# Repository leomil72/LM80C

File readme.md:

# LM80C Color Computer - A Z80-based homebrew computer

> This is the official repo of the **LM80C Color Computer**, an 8-bit home computer based on the Z80 CPU entirely developed since 2019 by **Leonardo Miliani**. Here you can find schematics, code and other stuff that you can use to replicate this project and build your own homebrew computer as a sort of "back to the old, good, days of 8-bit systems".
>
> Project main page: [LM80C](https://www.leonardomiliani.com/?page_id=1534&lang=en)
>
> Tags: z80, zilog, homebrew, 8-bits, computer, lm80c, ctc, pio, sio, tms9918a, ay-3-8910, ym2149f

---

## Getting started

- [Overview](#overview)
- [What you need](#what-you-need)
- [Folder organization](#folder-organization)
- [Compilation](#compilation)
- [Emulation](#emulation)
- [Z88DK Support](#Z88DK-Support)
- [FAQ](#faq)
- [Support](#support)
- [Donations](#donations)
- [License](#license)

---

## Overview

The **LM80C** is an 8-bit home-computer built around the Zilog Z80 CPU with video and audio capabilities. It's a stand-alone system thanks to its integrated keyboard that permits to use it without the necessity of host computers, usually used as input/output devices in other similar projects. With the LM80C BASIC you can write your own games, programs, and much more.

### Models
Actually, there is only one model of the computer: the **LM80C 64K Color Computer**. Originally, there was also the **LM80C Color Computer** but it has been considered as DEPRECATED and its developmente and/or supporto has been cheased. There were a couple of differences between the two: the former only had 32KB of SRAM and an interface to SD cards based on an Atmega328P as a mass storage (never developed, my fault), while the latter has 64KB of SRAM and a new mass storage interface based on Compat Flash cards, perfectly supported.

### Main features

  **LM80C 64K Color Computer**

- CPU: Zilog Z80B@3.68 MHz
- Memory:
  - ROM: 32KB (with built-in firmware & BASIC)
  - RAM: 64KB SRAM
- Video:
  - TMS9918A with 32KB of dedicated VRAM (2x 16K banks)
  - composite output
  - 256x192 pixels, 15 colors, 32 sprites
- Audio:
  - Yamaha YM2149F (or GI AY-3-8910)
  - 3 analog channels with tone&noise generation
  - envelope control
  - 2x8-bit I/O ports
- I/O capabilities:
  - Z80 PIO:
    - parallel input/output periphery
    - 2x8-bit ports
    - 4 operatin modes
  - Z80 SIO:
    - serial input/output periphery
    - 2 serial ports
    - higly configurable
    - software-adjustable baude rates
  - Z80 CTC:
    - timer/counter with 4 channels
   - generate system ticks and baud rates
- Keyboard:
  - external keyboard with 64 keys (I used a Commodore 16 keyboard, that has 66 keys but only 64 unique keys due to double connections for SHIFT and SHIFT/LOCK)
- Mass storage:
  - support for Compact Flash memory cards
    - disk formatting/renaming
    - load/save/erase of BASIC, binary, and sequential files;

Thanks to the bank switching mechanism implemented into the computer, the machine can use the whole amount of 64KB of SRAM. The same mechanism is used to provide 2x 16K banks of VRAM to the VDP so that 2 entire video framebuffers can be loaded and stored into the VRAM.

**LM80C Color Computer** (DEPRECATED)

- CPU: Zilog Z80B@3.68 MHz
- Memory:
  - ROM: 32KB (with built-in firmware & BASIC)
  - RAM: 32KB SRAM
- Video:
  - TMS9918A with 16KB of dedicated VRAM
  - composite output
  - 256x192 pixels, 15 colors, 32 sprites
- Audio:
  - Yamaha YM2149F (or GI AY-3-8910)
  - 3 analog channels with tone&noise generation
  - envelope control
  - 2x8-bit I/O ports
- I/O capabilities:
  - Z80 PIO:
    - parallel input/output periphery
    - 2x8-bit ports
    - 4 operatin modes
  - Z80 SIO:
    - serial input/output periphery
    - 2 serial ports
    - higly configurable
    - software-adjustable baude rates
  - Z80 CTC:
    - timer/counter with 4 channels
   - generate system ticks and baud rates
- Keyboard:
  - external keyboard with 64 keys (I used a Commodore 16 keyboard, that has 66 keys but only 64 unique keys due to double connections for SHIFT and SHIFT/LOCK)
- More to come:
  - support for SD memory cards

*IMPORTANT NOTE*: due to the release of the LM80C 64K model, the development of the LM80C has been halted. At the moment, only software improvements for the LM80C BASIC are still developed and ported from the bigger brother. Since this downgrade to a minor model, the support for SD cards is not developed anymore. The PCB is basically still printable but please don't populate the SD interface portion with any of the components since none of them will be used.

### BASIC

The **LM80C BASIC** is a dialect of the BASIC, a versatile and user-friendly programming language, the de-facto standard of the '80s since it was integrated into almost every 8-bit home computer. It derives from Nascom BASIC, that in turn derives from Microsoft Z80 BASIC 4.7. The LM80C BASIC is more than just a derivative language: in fact, it has its own set of commands and functions to take advantage of the specific LM80C hardware, like statements to draw point, lines, and circles, change foreground and background colors, move the cursor, play a tone or a noise, open/close the serial port, etc. It lets you to write good BASIC games, like "Lunar Lander", see below:

---

## What you need

Before to start building your own LM80C computer you need several things:
- of course, you need some hardware (electronic components, solder, breadboards, chips, etc.);
- some software (code editor & assembler);
- a CAD (to open schematics files and to generate Gerber files to make the PCB).
- some skills (you may be able to assemble a prototype, program it, burn a ROM file, etc.).

### Electronic parts
Passive electronic components can be grabbed anywhere: there are a lot of difference sources, like auction sites, big resellers, and local shops, too. The main chips, the Z80 family chips, are also widely available since the manufacturer, Zilogs, still continue to produce and commercialize them. More effort is needed to find the video and audio chips. The VDP and PSG are still available from China but, while the video chip is very common (in the past there has been over-production so a lot of spare components are still available), the audio chip is more rare and it is easy to find counterfit parts that doesn't work.

### Software
Personally I'm using [Visual Studio Code](https://code.visualstudio.com/) to write the ASM files: it's free, based on an open source project, and multi-platform (do not confuse with Visual Studio IDE). The extension to highlight the assembly code is [Z80 ASM](https://github.com/Imanolea/z80asm-vscode). Visual Code is a very complete editor and you can use for every language you use. Another good editor is [ATOM editor](https://atom.io) to edit the code, with [Language-assembler-SJASMPLUS](https://atom.io/packages/language-assembler-sjasmplus) package to highlight the Z80 assembly code. I prefer the former because it's lighter. 

To compile binaries I actually use [SJASMPlus](https://github.com/z00m128/sjasmplus), because it's multi-platform (MacOS/Linux/Windows) and has a lot of features, like macros, support for in-source LUA scripting, and much more. But you may use the assembler you want. However, for your commodity, the latest precompiled binary file, ready to be burned into an EEPROM, is always available.

To open/modify schematics you need a CAD: I use [KiCad](https://www.kicad.org/), that (IMHO) is the best choice, since it's free and doesn't have the limitations of the freeware version of [EagleCAD](https://www.autodesk.com/products/eagle/overview), that can't let you create a board bigger than 80 square cms., and the LM80C PCB is much bigger. However, I've also added PDF files if you just want to look at the schematics but don't want/need any additional software to open the schematics.

### Hardware
To burn the binaries on the (E)EPROM chips I used a modified version of [TommyPROM](https://github.com/leomil72/TommyPROM) so that I can use 74HCT595 shift registers, but you can use any (E)EPROM programmer you have. If you want to replicate my programmer, you need an [Arduino/Genuino Uno](https://www.arduino.cc) board. Please buy a *genuine board*, not a counterfit one, to help the open-source project. 

### Prototyping
I strongly recommend you to assemble a prototype on breadboards to be sure that everything is working right. The pictures below represent the LM80C during its development:

---

## Folder organization
The files in this repo are organized in folders:
- "12-Home Computer": this folder contains the main ASM file to compile the latest firmwares of the LM80C/LM80C 64K Color Computer.
- "BASIC examples": this folder contains BASIC programs that can be loaded and executed with the integrated LM80C BASIC interpreter. If the name contains a release version (i.e. R20), it means it's the minimum firmware release required to run such program, because it makes use of some statements not present in previous releases.
-  "Legacy": old firmware are stored into this folder. Folders whose names start with "01-" through "09-" contain the first tests I made with the computer without the video section, that you can replicate to work solely through the serial line. Folders whose names start with "10-" and "11-" contain the releases that had preliminary support for video output. "Legacy cores" contains the old firmwares of the latest hardware version of the computer. Every release adds some functionality to the original BASIC. The greater the release number is, the newer the firmware is.
- "Rom": this folder contains pre-compiled binary files, ready to be burned into the EEPROM chip, and ".lst" files.
- "Schematics": this folder contains the KiCad files of the current hardware revision of the computer, plus some PDF files including the complete schematics of the computer.
- "include": this folder contains the sub-folders with the files needed to compile the firmware. They are: "basic", "bootloader","psg", and "vdp". Each sub-folder contains the file of the corresponding module.
- "manuals": this folder contains useful manuals for the CPU, the peripheral chips, the video and audio chips, and a couple of  files that illustrate the main features of the LM80C and the reference manual of the LM80C BASIC language.

---

## Compilation
To compile the firmware, first download or clone the repo on your computer, than go into the "12-Home computer" folder, copy inside it the executable of SJAsmPlus specific for your OS, open a terminal in it, then give this command:
`./sjasmplus --lst --lstlab LM80-firmware-rx.yy.asm`

`./sjasmplus --lst --lstlab LM80C_64K-firmware-rx.yy.asm`

where "X.YY" is the release you want to compile. After the compilation has finished, you'll find a file with extension `.bin` that you can burn into the EEPROM. Another file with extension `.lst` is created: this is useful to get addresses of entry point functions and memory registers.

---

## Emulation
There is an [LM80C online emulator](https://github.com/nippur72/lm80c-emu), written in Javascript by Antonino Porcino, that can be used to see how the real machine acts and works: you can test directly in your browser by opening [this link](https://nippur72.github.io/lm80c-emu/). 
These are the latest releases that can be launched:

[LM80C with Z88DK support](https://nippur72.github.io/lm80c-emu/?rom=314)

[LM80C 3.19 (latest firmware for 32K model)](https://nippur72.github.io/lm80c-emu/?rom=319)

[LM80C 64K (with integrated DOS)](https://nippur72.github.io/lm80c-emu/?rom=64K119)

---

## Z88DK Support
The latest releases of [Z88DK](https://github.com/z88dk/z88dk) support the compilation of C programs for LM80C Color Computer. You need to grab one of the nightly build. After the compilation, a file with extesion `.prg` is basically a big file composed by a BASIC file that is just a simple loader that start the execution of a bigger machine language program. At the moment the compiled files only support the version R3.14 of the LM80C Color Computer and can be launched in the emulator by simply draggind them into the emulator window once launched it and then by typing RUN.

## FAQ

- **How can I clone this repo?**
  - On your desktop computer, by using a GUI frontend like SmartGit, or via a terminal by typing the following command ```git clone https://github.com/leomil72/LM80C```
  - Online, by clicking on the "Fork" button
- **How can I download the files?**
  - By clicking the green top-right "Clone or Download" and then by clicking on "Download ZIP"
- **How do I write and compile an ASM source file?**
  - You need an editor to write the source code and then an 'assembler' to compile the binary file. Please look at the "Software" section above.
- **How do I burn the binary file into the EEPROM?**
  - You need an (E)EPROM programmer, a device that can be connected to your computer and that can write the data into the memory chip. You can buy a programmer from internet or build your own device like me.
- **Where can I find the chips you're using in the LM80C computer?**
  - Zilog still manufactures the Z80 family chips, so you can get them from almost any good reseller, or, alternatively, new/used parts can be catched from online auctions sites. The 74HCTxx integrated are very common, so you shouldn't have any problem to grab them. The VDP and PSG chips are only available as used parts from several eastern resellers. Pay attention that you can easily buy a counterfit chip so if it won't work, before to think that your computer is badly assembled, try another part.
- **The software seems not to be working/the hardware I built following your schematics doesn't work: where can I find help? Can I write to you?**
  - The project is released "as is", without any warranty/responsability: despite I've tested it and I'm currently using it, I can not guarantee that it is completely error-free, nor that it can run with no issues for a relitively long time, nor that there are no errors in the code/schematic files that are online. So, please do NOT write me to complain about something's not working. Open an "issue" or a "pull request". Thank you.

---

## Support

You can find more about me on my website at <a href="https://www.leonardomiliani.com/?lang=en" target="_blank">www.leonardomiliani.com</a>.

---

## Donations

- If you want to help me maintain my site, my projects, and keep me rolling on, you may consider to make a small donation with <a href="https://www.paypal.me/LeonardoMiliani" target="_blank">Paypal</a>.

---

## License

- Some portions of code are copyright <a href="http://searle.hostei.com/grant/" target="_blank">Grant Searle</a>
- Some portions of code are copyright <a href="http://www.train­z.de" target="_blank">Mario Blunk</a>
- BASIC code is copyright <a href="http://www.microsoft.com" target="_blank">Microsoft</a>
- Some commercial names (like KiCAD, EagleCAD, Visual Studio Code) lead to the corresponding owners.
- The rest of the stuff is my own work and is distribuited under the [Gnu GPL Licence 3.0](https://opensource.org/licenses/GPL-3.0).

The names "LM80C", "LM80C 64K", "LM80C Color Computer", "LM80C 64K Color Computer", and "LM80C BASIC", the "rainbow LM80C" logo, the LM80C schematics, the LM80C sources, and this work belong to Leonardo Miliani. 

The "rainbow LM80C" logo and the "LM80C/LM80C Color Computer/LM80C 64K/LM80C 64K Color Computer" names can not be used in any work without my explicit permission. You are allowed to use the "LM80C" and "LM80C 64K" names only in reference to or to describe the LM80C/LM80C 64K Color Computers.

The LM80C/LM80C 64K schematics and source codes are released under the GNU GPL License 3.0 and in the form of "as is", without any kind of warranty: you can use them at your own risk. You are free to use them for any non-commercial use: you are only asked to maintain the copyright notices, to include this advice and, if you intend to re-distribute them, the note to the attribution of the original works to Leonardo Miliani. For any other use, please contact me by opening an issue.

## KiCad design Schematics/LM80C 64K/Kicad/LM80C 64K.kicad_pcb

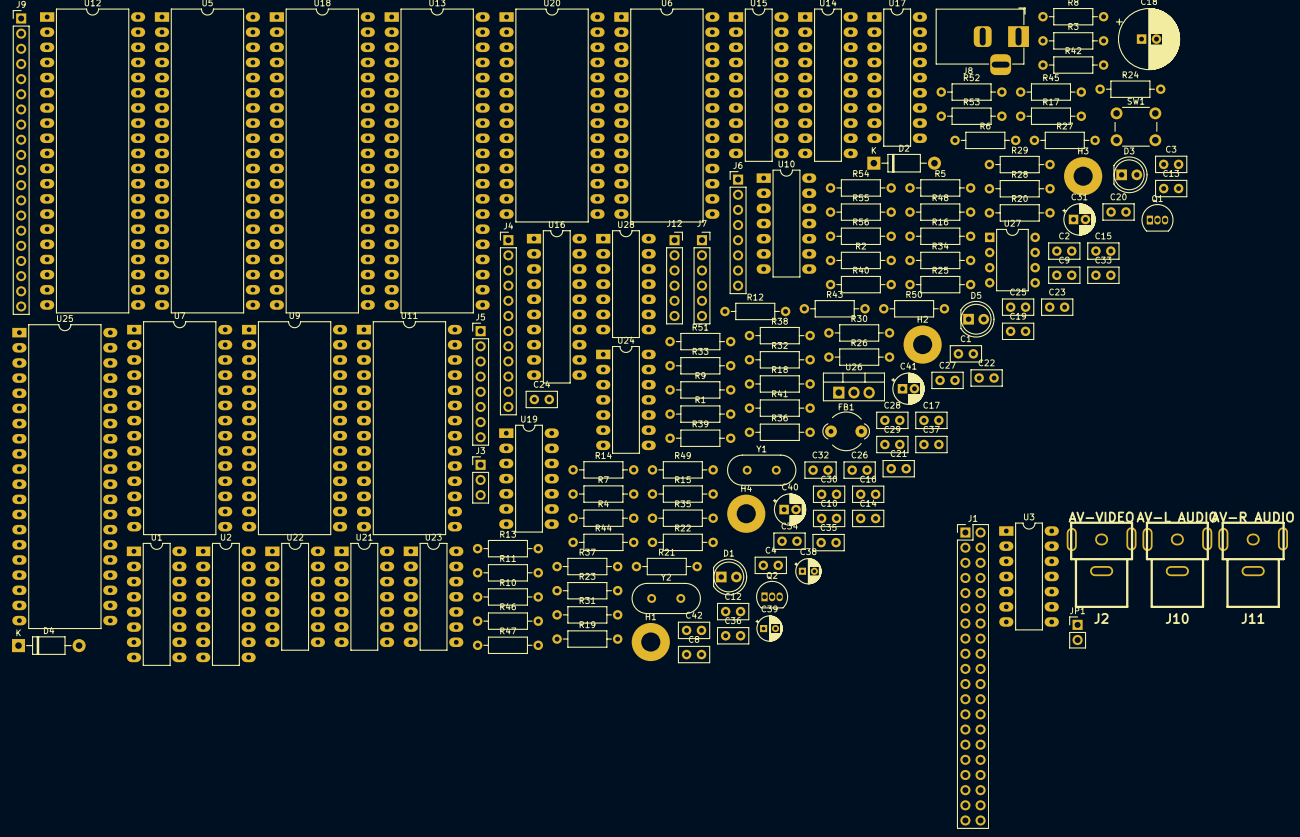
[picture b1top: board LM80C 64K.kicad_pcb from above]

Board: 2 copper layers, 148 parts (0 on the bottom side), 219 nets, no tracks yet.

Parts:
C1, C2, C3, C4, C8, C9, C10, C12, C13, C16, C17, C19, C20, C21, C22, C23, C24, C25, C26, C27, C28, C29, C30, C32, C33, C37, C42: 0.1u; C_Disc_D5.0mm_W2.5mm_P2.50mm
C14, C15: 33p; C_Disc_D5.0mm_W2.5mm_P2.50mm
C18: 220u; CP_Radial_D10.0mm_P2.50mm
C31: 100u; CP_Radial_D5.0mm_P2.00mm
C34, C35: 22p; C_Disc_D5.0mm_W2.5mm_P2.50mm
C36: 100n; C_Disc_D5.0mm_W2.5mm_P2.50mm
C38, C39: 100u; CP_Radial_D4.0mm_P2.00mm
C40, C41: 10u; CP_Radial_D5.0mm_P2.00mm
D1, D3, D5: LED; LED_D5.0mm
D2, D4: 1N4007; D_DO-41_SOD81_P10.16mm_Horizontal
FB1: Ferrite_Bead; LairdTech_28C0236-0JW-10
H1, H2, H3, H4: MountingHole_Pad; MountingHole_3.2mm_M3_Pad
J1: Conn_02x20_Odd_Even; PinHeader_2x20_P2.54mm_Vertical
J2: AV-VIDEO; RCAsimple
J3: Conn_01x03; PinHeader_1x03_P2.54mm_Vertical
J4: Conn_01x12; PinHeader_1x12_P2.54mm_Vertical
J5, J6: Conn_01x08_Male; PinHeader_1x08_P2.54mm_Vertical
J7, J12: FT232 CONN; PinSocket_1x06_P2.54mm_Vertical
J8: Barrel_Jack_Switch; BarrelJack_Horizontal
J9: Conn_01x20; PinHeader_1x20_P2.54mm_Vertical
J10: AV-L AUDIO; RCAsimple
J11: AV-R AUDIO; RCAsimple
JP1: Jumper; PinHeader_1x02_P2.54mm_Vertical
Q1: 2N3904; TO-92_Inline
Q2: BC337; TO-92_Inline
R1, R2, R6, R8, R11, R20, R21, R22, R31, R34, R36, R37, R51: 10K; R_Axial_DIN0207_L6.3mm_D2.5mm_P10.16mm_Horizontal
R3, R5, R32, R33, R35, R48, R49, R55, R56: 2K7; R_Axial_DIN0207_L6.3mm_D2.5mm_P10.16mm_Horizontal
R4, R38, R41, R44, R46, R47, R53: 1K; R_Axial_DIN0207_L6.3mm_D2.5mm_P10.16mm_Horizontal
R7: 470R; R_Axial_DIN0207_L6.3mm_D2.5mm_P10.16mm_Horizontal
R9, R10: 75R; R_Axial_DIN0207_L6.3mm_D2.5mm_P10.16mm_Horizontal
R12, R13, R14, R15, R16, R17, R18, R19: 390R; R_Axial_DIN0207_L6.3mm_D2.5mm_P10.16mm_Horizontal
R23, R24, R25, R26, R27, R28, R29, R30, R54: 330R; R_Axial_DIN0207_L6.3mm_D2.5mm_P10.16mm_Horizontal
R39: 100K; R_Axial_DIN0207_L6.3mm_D2.5mm_P10.16mm_Horizontal
R40: 8M2; R_Axial_DIN0207_L6.3mm_D2.5mm_P10.16mm_Horizontal
R42, R43: 2K2; R_Axial_DIN0207_L6.3mm_D2.5mm_P10.16mm_Horizontal
R45: 330; R_Axial_DIN0207_L6.3mm_D2.5mm_P10.16mm_Horizontal
R50: 47K; R_Axial_DIN0207_L6.3mm_D2.5mm_P10.16mm_Horizontal
R52: 470; R_Axial_DIN0207_L6.3mm_D2.5mm_P10.16mm_Horizontal
SW1: SW_DIP_x01; SW_PUSH_6mm_H4.3mm
U1: 74HCT139; DIP-16_W7.62mm_LongPads
U2: 74HCT138; DIP-16_W7.62mm_LongPads
U3, U22: 74HCT32; DIP-14_W7.62mm_LongPads
U5: Z80-CPU; DIP-40_W15.24mm_LongPads
U6, U7: HM62256BLP-12; DIP-28_W15.24mm_LongPads
U9: 28C256; DIP-28_W15.24mm_LongPads
U10: 74HCT08; DIP-14_W7.62mm_LongPads
U11: Z80-CTC; DIP-28_W15.24mm_LongPads
U12: Z80-PIO; DIP-40_W15.24mm_LongPads
U13: TMS9918A; DIP-40_W15.24mm_LongPads
U14, U15, U16: 74HCT574; DIP-20_W7.62mm_LongPads
U17: ULN2803A; DIP-18_W7.62mm_LongPads
U18: Z80-SIO_0; DIP-40_W15.24mm_LongPads
U19, U23: 74HCT04; DIP-14_W7.62mm_LongPads
U20: HM62256BLP-7; DIP-28_W15.24mm_LongPads
U21: 4066; DIP-14_W7.62mm_LongPads
U24: 74HC02; DIP-14_W7.62mm_LongPads
U25: AY-3-8910; DIP-40_W15.24mm_LongPads
U26: LM317_3PinPackage; TO-220-3_Vertical
U27: NE555P; DIP-8_W7.62mm
U28: 74HCT74; DIP-14_W7.62mm_LongPads
Y1: 10.738635MHz; Crystal_HC49-4H_Vertical
Y2: 7.372800MHz; Crystal_HC49-4H_Vertical

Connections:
+5V: C1.2, C2.1, C3.1, C4.1, C8.1, C9.1, C10.2, C12.2, C13.1, C17.2, C19.2, C20.2, C21.2, C22.2, C23.1, C24.2, C25.1, C26.2, C27.1, C28.1, C29.1, C30.1, C36.1, C37.1, C40.1, C42.1, D4.2, D5.2, FB1.1, J1.20, J4.1, J6.1, J6.2, J6.3, J6.4, J6.5, J6.6, J6.7, J6.8, R1.2, R2.2, R4.1, R6.2, R8.1, R11.1, R20.2, R21.1, R31.1, R34.2, R39.1, R45.2, R50.1, R51.1, U1.16, U2.16, U3.14, U5.11, U6.28, U7.28, U9.28, U10.14, U11.24, U12.26, U13.33, U14.20, U15.20, U16.20, U18.9, U19.14, U20.28, U21.14, U22.14, U23.14, U24.14, U25.25, U25.28, U25.40, U26.2, U27.4, U27.8, U28.1, U28.4, U28.10, U28.13, U28.14
+9V: D2.2, J8.1
/A3: U5.33, U6.7, U7.7, U9.7
/A8: U5.38, U6.25, U7.25, U9.25
/A9: U5.39, U6.24, U7.24, U9.24
/A10: U5.40, U6.21, U7.21, U9.21
/A11: U5.1, U6.23, U7.23, U9.23
/A12: U5.2, U6.2, U7.2, U9.2
/A13: U5.3, U6.26, U7.26, U9.26
/A14: U5.4, U6.1, U7.1, U9.1
/AD0: U13.10, U14.2, U15.2, U16.2
/AD1: U13.9, U14.3, U15.3, U16.3
/AD2: U13.8, U14.4, U15.4, U16.4
/AD3: U13.7, U14.5, U15.5, U16.5
/AD4: U13.6, U14.6, U15.6, U16.6
/AD5: U13.5, U14.7, U15.7, U16.7
/AD6: U13.4, U14.8, U15.8, U16.8
/AD7: U13.3, U14.9, U15.9, U16.9
/VA0: U14.18, U20.10
/VA1: U14.17, U20.9
/VA2: U14.16, U20.8
/VA3: U14.15, U20.7
/VA4: U14.14, U20.21
/VA5: U14.13, U20.6
/VA6: U14.12, U20.5
/VA7: U15.18, U20.23
/VA8: U15.17, U20.4
/VA9: U15.16, U20.3
/VA10: U15.15, U20.24
/VA11: U15.14, U20.2
/VA12: U15.13, U20.25
/VA13: U15.12, U20.26
/VD0: U13.32, U16.19, U20.11
/VD1: U13.31, U16.18, U20.12
/VD2: U13.30, U16.17, U20.13
/VD3: U13.29, U16.16, U20.15
/VD4: U13.28, U16.15, U20.16
/VD5: U13.27, U16.14, U20.17
/VD6: U13.26, U16.13, U20.18
/VD7: U13.25, U16.12, U20.19
A0: J1.35, U5.30, U6.10, U7.10, U9.10, U11.18, U12.6, U18.34, U24.8
A1: J1.33, U5.31, U6.9, U7.9, U9.9, U11.19, U12.5, U13.13, U18.33
A2: J1.36, U5.32, U6.8, U7.8, U9.8
A4: U2.1, U5.34, U6.6, U7.6, U9.6
A5: U2.2, U5.35, U6.5, U7.5, U9.5
A6: U2.3, U5.36, U6.4, U7.4, U9.4
A7: U2.5, U5.37, U6.3, U7.3, U9.3
A15: U1.2, U5.5
BANK1_SEL: U1.4, U1.15
CAS: U13.2, U19.1, U20.20
CF_SEL: J1.37, U2.10
CLK2: U11.22, U11.23, U25.22, U28.9
CLOCK: U5.6, U11.15, U12.25, U18.20, U28.5, U28.11
COL: U15.11, U19.6
COMVID: Q1.2, R7.1, U13.36
CSR: U13.15, U22.6
CSW: U13.14, U22.8
CTC_IE: U11.13, U18.7
CTC_SEL: U2.14, U11.16
D0: J1.17, U5.14, U6.11, U7.11, U9.11, U11.25, U12.19, U13.17, U18.40, U25.37
D1: J1.15, U5.15, U6.12, U7.12, U9.12, U11.26, U12.20, U13.18, U18.1, U25.36
D2: J1.13, U5.12, U6.13, U7.13, U9.13, U11.27, U12.1, U13.19, U18.39, U25.35
D3: J1.11, U5.8, U6.15, U7.15, U9.15, U11.28, U12.40, U13.20, U18.2, U25.34
D4: J1.9, U5.7, U6.16, U7.16, U9.16, U11.1, U12.39, U13.21, U18.38, U25.33
D5: J1.7, U5.9, U6.17, U7.17, U9.17, U11.2, U12.38, U13.22, U18.3, U25.32
D6: J1.5, U5.10, U6.18, U7.18, U9.18, U11.3, U12.3, U13.23, U18.37, U25.31
D7: J1.3, U5.13, U6.19, U7.19, U9.19, U11.4, U12.2, U13.24, U18.4, U25.30
EN_SWC: U10.6, U21.5, U21.6, U21.12, U21.13
GND: C1.1, C2.2, C3.2, C4.2, C8.2, C9.2, C10.1, C12.1, C13.2, C14.1, C15.1, C16.2, C17.1, C19.1, C20.1, C21.1, C22.1, C23.2, C24.1, C25.2, C26.1, C27.2, C28.2, C29.2, C30.2, C31.2, C32.2, C33.2, C34.2, C35.2, C36.2, C37.2, C40.2, C41.2, C42.2, D1.1, D3.1, J1.2, J1.19, J1.22, J1.24, J1.26, J1.30, J1.40, J2.2, J4.2, J7.1, J8.2, J8.3, J10.2, J11.2, J12.1, Q2.3, R7.2, R9.2, R22.1, R36.2, R37.2, R46.1, R48.1, R49.1, SW1.1, U1.3, U1.8, U1.13, U2.8, U3.7, U5.29, U6.14, U7.14, U9.14, U10.7, U11.5, U12.11, U13.12, U14.1, U14.10, U15.1, U15.10, U16.10, U17.9, U18.18, U18.19, U18.22, U18.23, U18.31, U19.7, U20.14, U21.7, U22.7, U23.7, U24.7, U25.24, U27.1, U28.7
INT: R11.2, U5.16, U11.12, U12.23, U18.5
IORQ: U2.4, U3.2, U3.4, U5.20, U11.10, U12.36, U18.36, U22.2
IO_RD: J1.25, U3.3
IO_WR: J1.23, U3.6
M1: U5.27, U10.2, U11.14, U18.8
MREQ: U1.1, U2.6, U5.19
unnamed: C14.2, U13.39, Y1.1
unnamed: C15.2, U13.40, Y1.2
unnamed: C16.1, FB1.2, Q1.3
unnamed: C18.1, R10.1
unnamed: C18.2, J2.1
unnamed: C31.1, C32.1, D2.1, D4.1, R38.2, U26.3
unnamed: C33.1, R39.2, SW1.2, U27.2
unnamed: C34.1, R40.2, U23.11, Y2.1
unnamed: C35.1, R40.1, R47.1, Y2.2
unnamed: C38.1, R41.2, R42.2, R48.2
unnamed: C38.2, J10.1
unnamed: C39.1, R43.2, R44.2, R49.2
unnamed: C39.2, J11.1
unnamed: C41.1, R50.2, U27.6, U27.7
unnamed: D1.2, R3.2
unnamed: D3.2, R38.1
unnamed: D5.1, R54.1
unnamed: J1.38, R4.2
unnamed: J1.39, JP1.2
unnamed: J3.1, U11.21
unnamed: J3.2, U11.9
unnamed: J3.3, U11.20
unnamed: J4.3, U12.18
unnamed: J4.4, U12.16
unnamed: J4.5, U12.15
unnamed: J4.6, U12.14
unnamed: J4.7, U12.13
unnamed: J4.8, U12.12
unnamed: J4.9, U12.10
unnamed: J4.10, U12.9
unnamed: J4.11, U12.8
unnamed: J4.12, U12.7
unnamed: J5.1, R23.1
unnamed: J5.2, R24.1
unnamed: J5.3, R25.1
unnamed: J5.4, R26.1
unnamed: J5.5, R27.1
unnamed: J5.6, R28.1
unnamed: J5.7, R29.1
unnamed: J5.8, R30.1
unnamed: J7.2, U21.2
unnamed: J7.4, U21.4
unnamed: J7.5, U21.9
unnamed: J7.6, U21.10
unnamed: J9.1, U25.8
unnamed: J9.3, U25.18
unnamed: J9.6, U25.13
unnamed: J9.7, U25.17
unnamed: J9.8, U25.12
unnamed: J9.9, U25.16
unnamed: J9.10, U25.15
unnamed: J9.11, U25.10
unnamed: J9.12, U25.11
unnamed: J9.13, U25.9
unnamed: J9.14, U25.19
unnamed: J9.15, U25.20
unnamed: J9.16, U25.7
unnamed: J9.17, U25.14
unnamed: J9.18, U25.21
unnamed: J9.19, U25.6
unnamed: J12.2, R5.1
unnamed: J12.4, R55.1
unnamed: J12.5, R56.1
unnamed: J12.6, U18.25
unnamed: JP1.1, R3.1
unnamed: Q1.1, R9.1, R10.2
unnamed: Q2.1, R54.2
unnamed: Q2.2, R53.1
unnamed: R1.1, U5.24
unnamed: R2.1, U5.25
unnamed: R5.2, U18.24
unnamed: R6.1, U9.27
unnamed: R12.1, U12.27
unnamed: R13.1, U12.28
unnamed: R14.1, U12.29
unnamed: R14.2, U17.6
unnamed: R15.1, U12.30
unnamed: R15.2, U17.5
unnamed: R16.1, U12.31
unnamed: R17.1, U12.32
unnamed: R17.2, U17.3
unnamed: R18.1, U12.33
unnamed: R19.1, U12.34
unnamed: R19.2, U17.1
unnamed: R21.2, U18.6
unnamed: R23.2, U17.18
unnamed: R24.2, U17.17
unnamed: R25.2, U17.16
unnamed: R26.2, U17.15
unnamed: R27.2, U17.14
unnamed: R28.2, U17.13
unnamed: R29.2, U17.12
unnamed: R30.2, U17.11
unnamed: R31.2, U18.11
unnamed: R32.1, U21.3
unnamed: R32.2, U18.12
unnamed: R33.1, U21.1
unnamed: R33.2, U18.17
unnamed: R34.1, U18.29
unnamed: R35.1, U21.8
unnamed: R35.2, U18.15
unnamed: R41.1, U25.3
unnamed: R42.1, R43.1, U25.38
unnamed: R44.1, U25.4
unnamed: R45.1, R46.2, U26.1
unnamed: R47.2, U23.10, U23.13
unnamed: R52.1, U10.9, U10.10
unnamed: R53.2, U10.8
unnamed: R55.2, U18.28
unnamed: R56.2, U18.26
unnamed: U10.3, U12.37
unnamed: U10.5, U23.4
unnamed: U18.16, U21.11
unnamed: U19.2, U19.3
unnamed: U19.4, U19.5
unnamed: U22.3, U22.4, U22.9
unnamed: U23.1, U27.3
unnamed: U23.12, U28.3
unnamed: U24.10, U25.29
unnamed: U24.13, U25.27
unnamed: U28.2, U28.6
unnamed: U28.8, U28.12
PIO_IE: U11.11, U12.24
PIO_SEL: U2.15, U12.4
PSG_SEL: U2.11, U24.9, U24.11
RAM1_SEL: U1.12, U6.20
RAM2_SEL: U1.5, U7.20
RAS: U13.1, U19.9
RD: U3.1, U5.21, U6.22, U7.22, U9.22, U11.6, U12.35, U18.32, U22.5
RESET: J1.1, R51.2, R52.2, U5.26, U10.1, U11.17, U13.34, U18.21, U23.2, U25.23
ROMSEL: U1.11, U9.20
ROM_RAM_1: R12.2, R20.1, U1.14, U17.8
ROW: U14.11, U19.8
SER1_ERR: R16.2, R37.1, U17.4, U23.3
SER1_OPN: R18.2, R36.1, U10.4, U17.2
SER_CLK_B: U11.8, U18.27
SIO_SEL: U2.13, U18.35
SRL_CLK_A: U11.7, U18.13, U18.14
VDP_INT: R8.2, U5.17, U13.16
VDP_SEL: U2.12, U22.1
VRAM_BANK: R13.2, R22.2, U17.7, U20.1
VRW: U13.11, U16.1, U19.11, U20.27
VWR: U16.11, U19.10, U20.22
WR: U3.5, U5.22, U6.27, U7.27, U22.10, U24.12

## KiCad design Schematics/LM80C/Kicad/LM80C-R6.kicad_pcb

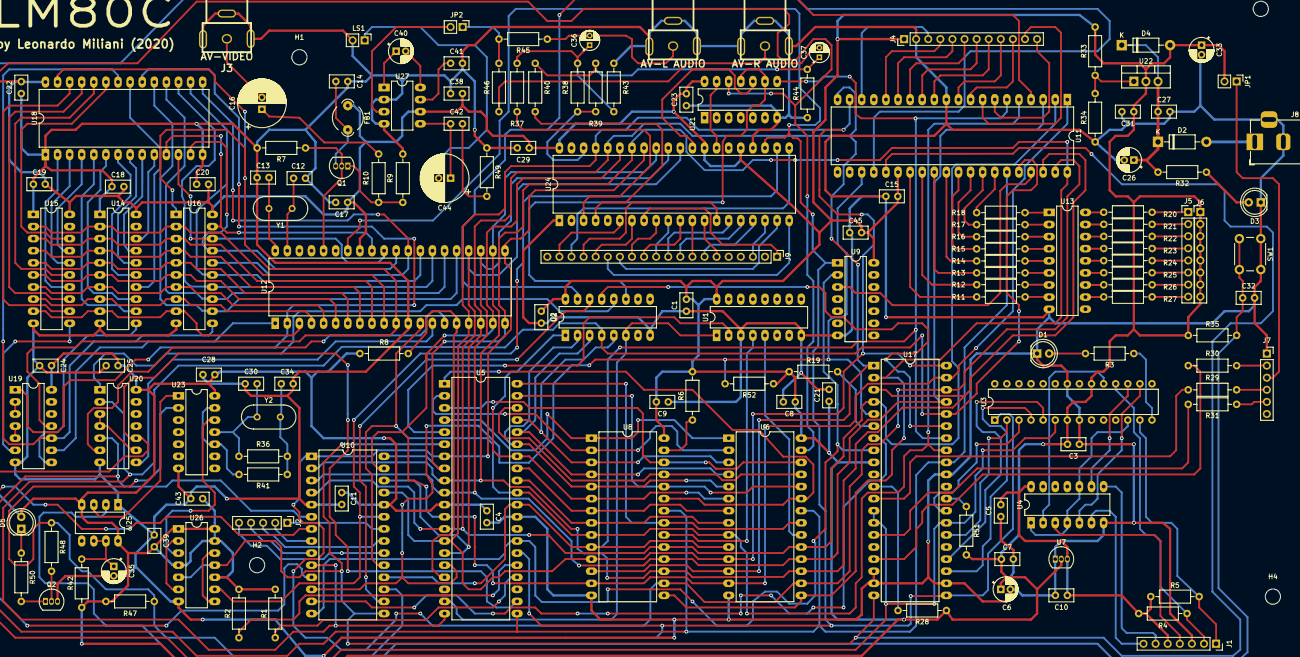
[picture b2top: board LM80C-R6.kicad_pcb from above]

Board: 2 copper layers, 153 parts (0 on the bottom side), 220 nets.

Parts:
C1, C2, C3, C4, C5, C7, C8, C9, C10, C11, C14, C15, C17, C18, C19, C20, C21, C22, C23, C24, C25, C27, C28, C29, C31, C32, C43, C45: 0.1u; C_Disc_D5.0mm_W2.5mm_P2.50mm
C6: 1u; CP_Radial_D5.0mm_P2.00mm
C12, C13: 33p; C_Disc_D5.0mm_W2.5mm_P2.50mm
C16, C44: 220u; CP_Radial_D10.0mm_P2.50mm
C26: 100u; CP_Radial_D5.0mm_P2.00mm
C30, C34: 22p; C_Disc_D5.0mm_W2.5mm_P2.50mm
C33, C35, C40: 10u; CP_Radial_D5.0mm_P2.00mm
C36, C37: 100u; CP_Radial_D4.0mm_P2.00mm
C38, C39, C41: 100n; C_Disc_D5.0mm_W2.5mm_P2.50mm
C42: 50n; C_Disc_D5.0mm_W2.5mm_P2.50mm
D1, D3, D5: LED; LED_D5.0mm
D2, D4: 1N4007; D_DO-41_SOD81_P10.16mm_Horizontal
FB1: Ferrite_Bead; LairdTech_28C0236-0JW-10
H1, H2, H3, H4: MountingHole_Pad; MountingHole_3.2mm_M3
J1: Conn_01x07_Female; PinSocket_1x07_P2.54mm_Vertical
J2: Conn_01x05; PinHeader_1x05_P2.54mm_Vertical
J3: AV-VIDEO; RCAsimple
J4: Conn_01x12; PinHeader_1x12_P2.54mm_Vertical
J5, J6: Conn_01x08_Male; PinHeader_1x08_P2.54mm_Vertical
J7: FT232 CONN; PinSocket_1x06_P2.54mm_Vertical
J8: Barrel_Jack_Switch; BarrelJack_Horizontal
J9: Conn_01x20; PinHeader_1x20_P2.54mm_Vertical
J10: AV-L AUDIO; RCAsimple
J11: AV-R AUDIO; RCAsimple
JP1, JP2: Jumper; PinHeader_1x02_P2.54mm_Vertical
LS1: Speaker; PinHeader_1x02_P2.54mm_Vertical
Q1: 2N3904; TO-92_Inline
Q2: BC337; TO-92_Inline
R1, R2, R4, R5, R6, R8, R19, R28, R47, R51, R52: 10K; R_Axial_DIN0207_L6.3mm_D2.5mm_P10.16mm_Horizontal
R3: 680; R_Axial_DIN0207_L6.3mm_D2.5mm_P10.16mm_Horizontal
R7: 470R; R_Axial_DIN0207_L6.3mm_D2.5mm_P10.16mm_Horizontal
R9, R10: 75R; R_Axial_DIN0207_L6.3mm_D2.5mm_P10.16mm_Horizontal
R11, R12, R13, R14, R15, R16, R17, R18: 390R; R_Axial_DIN0207_L6.3mm_D2.5mm_P10.16mm_Horizontal
R20, R21, R22, R23, R24, R25, R26, R27, R50: 330R; R_Axial_DIN0207_L6.3mm_D2.5mm_P10.16mm_Horizontal
R29, R30, R31, R43, R44: 2K7; R_Axial_DIN0207_L6.3mm_D2.5mm_P10.16mm_Horizontal
R32, R34, R37, R40, R41, R45, R46, R48: 1K; R_Axial_DIN0207_L6.3mm_D2.5mm_P10.16mm_Horizontal
R33: 330; R_Axial_DIN0207_L6.3mm_D2.5mm_P10.16mm_Horizontal
R35: 100K; R_Axial_DIN0207_L6.3mm_D2.5mm_P10.16mm_Horizontal
R36: 8M2; R_Axial_DIN0207_L6.3mm_D2.5mm_P10.16mm_Horizontal
R38, R39: 2K2; R_Axial_DIN0207_L6.3mm_D2.5mm_P10.16mm_Horizontal
R42: 47K; R_Axial_DIN0207_L6.3mm_D2.5mm_P10.16mm_Horizontal
R49: 10R; R_Axial_DIN0207_L6.3mm_D2.5mm_P10.16mm_Horizontal
SW1: SW_DIP_x01; SW_PUSH_6mm_H4.3mm
U1: 74HCT139; DIP-16_W7.62mm_LongPads
U2: 74HCT138; DIP-16_W7.62mm_LongPads
U3: ATmega328P-PU; DIP-28_W7.62mm
U4: 74HCT125; DIP-14_W7.62mm_LongPads
U5: Z80-CPU; DIP-40_W15.24mm_LongPads
U6: HM62256BLP-12; DIP-28_W15.24mm_LongPads
U7: MCP1700-3302E_TO92; TO-92_Inline
U8: 28C256; DIP-28_W15.24mm_LongPads
U9: 74HCT08; DIP-14_W7.62mm_LongPads
U10: Z80-CTC; DIP-28_W15.24mm_LongPads
U11: Z80-PIO; DIP-40_W15.24mm_LongPads
U12: TMS9918A; DIP-40_W15.24mm_LongPads
U13: ULN2803A; DIP-18_W7.62mm_LongPads
U14, U15, U16: 74HCT574; DIP-20_W7.62mm_LongPads
U17: Z80-SIO_0; DIP-40_W15.24mm_LongPads
U18: HM62256BLP-7; DIP-28_W15.24mm_LongPads
U19, U23: 74HCT04; DIP-14_W7.62mm_LongPads
U20: 74HCT32; DIP-14_W7.62mm_LongPads
U21: 74HC02; DIP-14_W7.62mm_LongPads
U22: LM317_3PinPackage; TO-220-3_Vertical
U24: AY-3-8910; DIP-40_W15.24mm_LongPads
U25: NE555; DIP-8_W7.62mm_LongPads
U26: 74HCT74; DIP-14_W7.62mm_LongPads
U27: LM386; DIP-8_W7.62mm_LongPads
Y1: 10.738635MHz; Crystal_HC49-4H_Vertical
Y2: 7.372800MHz; Crystal_HC49-4H_Vertical

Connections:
+3V3: C5.1, C10.1, J1.5, R4.1, R5.1, U4.14, U7.3
+5V: C1.2, C2.1, C3.2, C4.1, C6.1, C7.1, C8.1, C9.2, C11.1, C15.2, C17.2, C18.2, C19.2, C20.2, C21.1, C22.2, C23.2, C24.1, C25.1, C28.1, C29.1, C31.1, C33.1, C38.2, C39.2, C43.1, C45.2, D4.2, D5.2, FB1.1, J4.1, J6.1, J6.2, J6.3, J6.4, J6.5, J6.6, J6.7, J6.8, JP1.2, R1.2, R2.2, R6.2, R8.1, R19.1, R28.1, R33.2, R35.1, R42.1, R47.1, R51.1, R52.1, U1.16, U2.16, U3.7, U3.20, U5.11, U6.28, U7.2, U8.28, U9.14, U10.24, U11.26, U12.33, U14.20, U15.20, U16.20, U17.9, U18.28, U19.14, U20.14, U21.14, U22.2, U23.14, U24.25, U24.28, U24.40, U25.4, U25.8, U26.1, U26.4, U26.10, U26.13, U26.14, U27.6
+9V: D2.2, J8.1
/A2: U5.32, U6.8, U8.8
/A3: U5.33, U6.7, U8.7
/A8: U5.38, U6.25, U8.25
/A9: U5.39, U6.24, U8.24
/A10: U5.40, U6.21, U8.21
/A11: U5.1, U6.23, U8.23
/A12: U5.2, U6.2, U8.2
/A13: U5.3, U6.26, U8.26
/A14: U5.4, U6.1, U8.1
/AD0: U12.10, U14.2, U15.2, U16.2
/AD1: U12.9, U14.3, U15.3, U16.3
/AD2: U12.8, U14.4, U15.4, U16.4
/AD3: U12.7, U14.5, U15.5, U16.5
/AD4: U12.6, U14.6, U15.6, U16.6
/AD5: U12.5, U14.7, U15.7, U16.7
/AD6: U12.4, U14.8, U15.8, U16.8
/AD7: U12.3, U14.9, U15.9, U16.9
/D0: U5.14, U6.11, U8.11, U10.25, U11.19, U12.17, U17.40, U24.37
/D1: U5.15, U6.12, U8.12, U10.26, U11.20, U12.18, U17.1, U24.36
/D2: U5.12, U6.13, U8.13, U10.27, U11.1, U12.19, U17.39, U24.35
/D3: U5.8, U6.15, U8.15, U10.28, U11.40, U12.20, U17.2, U24.34
/D4: U5.7, U6.16, U8.16, U10.1, U11.39, U12.21, U17.38, U24.33
/D5: U5.9, U6.17, U8.17, U10.2, U11.38, U12.22, U17.3, U24.32
/D6: U5.10, U6.18, U8.18, U10.3, U11.3, U12.23, U17.37, U24.31
/D7: U5.13, U6.19, U8.19, U10.4, U11.2, U12.24, U17.4, U24.30
/VA0: U14.18, U18.10
/VA1: U14.17, U18.9
/VA2: U14.16, U18.8
/VA3: U14.15, U18.7
/VA4: U14.14, U18.21
/VA5: U14.13, U18.6
/VA6: U14.12, U18.5
/VA7: U15.18, U18.23
/VA8: U15.17, U18.4
/VA9: U15.16, U18.3
/VA10: U15.15, U18.24
/VA11: U15.14, U18.2
/VA12: U15.13, U18.25
/VA13: U15.12, U18.26
/VD0: U12.32, U16.19, U18.11
/VD1: U12.31, U16.18, U18.12
/VD2: U12.30, U16.17, U18.13
/VD3: U12.29, U16.16, U18.15
/VD4: U12.28, U16.15, U18.16
/VD5: U12.27, U16.14, U18.17
/VD6: U12.26, U16.13, U18.18
/VD7: U12.25, U16.12, U18.19
A0: U5.30, U6.10, U8.10, U10.18, U11.6, U17.34, U21.8
A1: U5.31, U6.9, U8.9, U10.19, U11.5, U12.13, U17.33
A4: U2.1, U5.34, U6.6, U8.6
A5: U2.2, U5.35, U6.5, U8.5
A6: U2.3, U5.36, U6.4, U8.4
A7: U2.5, U5.37, U6.3, U8.3
A15: U1.2, U5.5
CAS: U12.2, U18.20, U19.1
CLK2: U10.23, U24.22, U26.9
CLOCK: U5.6, U10.15, U11.25, U17.20, U26.5, U26.11
COL: U15.11, U19.6
COMVID: Q1.2, R7.1, U12.36
CSR: U12.15, U20.6
CSW: U12.14, U20.8
CTC_IE: U10.13, U17.7
CTC_SEL: U2.14, U10.16
CTSB: U3.4, U17.23
GND: C1.1, C2.2, C3.1, C4.2, C5.2, C6.2, C7.2, C8.2, C9.1, C10.2, C11.2, C12.1, C13.1, C14.2, C15.1, C17.1, C18.1, C19.1, C20.1, C21.2, C22.1, C23.1, C24.2, C25.2, C26.2, C27.2, C28.2, C29.2, C30.2, C31.2, C32.2, C33.2, C34.2, C35.2, C38.1, C39.1, C41.2, C43.2, C45.1, D1.1, D3.1, J1.3, J3.2, J4.2, J7.1, J8.2, J8.3, J10.2, J11.2, LS1.2, Q2.3, R7.2, R9.2, R34.1, R43.1, R44.1, R49.1, SW1.1, U1.3, U1.8, U2.8, U3.8, U3.22, U4.7, U5.29, U6.14, U7.1, U8.14, U9.7, U10.5, U11.11, U12.12, U13.9, U14.1, U14.10, U15.1, U15.10, U16.10, U17.18, U17.19, U17.22, U17.31, U18.1, U18.14, U19.7, U20.7, U21.7, U23.7, U24.1, U24.24, U25.1, U26.7, U27.2, U27.4
INT: R52.2, U5.16, U10.12, U11.23, U17.5
IORQ: U2.4, U5.20, U10.10, U11.36, U17.36, U20.2
M1: U5.27, U9.2, U10.14, U17.8
MISO: J1.2, R4.2, U3.18
MOSI: U3.17, U4.9
MREQ: U1.1, U2.6, U5.19
unnamed: C12.2, U12.39, Y1.1
unnamed: C13.2, U12.40, Y1.2
unnamed: C14.1, FB1.2, Q1.3
unnamed: C16.1, R10.1
unnamed: C16.2, J3.1
unnamed: C26.1, C27.1, D2.1, D4.1, R32.2, U22.3
unnamed: C30.1, R36.2, U23.11, Y2.1
unnamed: C32.1, R35.2, SW1.2, U25.2
unnamed: C34.1, R36.1, R41.1, Y2.2
unnamed: C35.1, R42.2, U25.6, U25.7
unnamed: C36.1, R37.2, R38.2, R43.2
unnamed: C36.2, J10.1, R45.1
unnamed: C37.1, R39.2, R40.2, R44.2
unnamed: C37.2, J11.1, R46.2
unnamed: C40.1, U27.1
unnamed: C40.2, U27.8
unnamed: C41.1, U27.7
unnamed: C42.1, C44.1, U27.5
unnamed: C42.2, R49.2
unnamed: C44.2, LS1.1
unnamed: D1.2, R3.2
unnamed: D3.2, R32.1
unnamed: D5.1, R50.1
unnamed: J1.4, U4.3
unnamed: J1.6, U4.8
unnamed: J1.7, U4.6
unnamed: J2.1, U10.22
unnamed: J2.2, U10.8
unnamed: J2.3, U10.21
unnamed: J2.4, U10.9
unnamed: J2.5, U10.20
unnamed: J4.3, U11.18
unnamed: J4.4, U11.16
unnamed: J4.5, U11.15
unnamed: J4.6, U11.14
unnamed: J4.7, U11.13
unnamed: J4.8, U11.12
unnamed: J4.9, U11.10
unnamed: J4.10, U11.9
unnamed: J4.11, U11.8
unnamed: J4.12, U11.7
unnamed: J5.1, R20.1
unnamed: J5.2, R21.1
unnamed: J5.3, R22.1
unnamed: J5.4, R23.1
unnamed: J5.5, R24.1
unnamed: J5.6, R25.1
unnamed: J5.7, R26.1
unnamed: J5.8, R27.1
unnamed: J7.2, R30.1
unnamed: J7.3, JP1.1
unnamed: J7.4, R29.1
unnamed: J7.5, R31.1
unnamed: J9.1, U24.8
unnamed: J9.3, U24.18
unnamed: J9.6, U24.13
unnamed: J9.7, U24.17
unnamed: J9.8, U24.12
unnamed: J9.9, U24.16
unnamed: J9.10, U24.15
unnamed: J9.11, U24.10
unnamed: J9.12, U24.11
unnamed: J9.13, U24.9
unnamed: J9.14, U24.19
unnamed: J9.15, U24.20
unnamed: J9.16, U24.7
unnamed: J9.17, U24.14
unnamed: J9.18, U24.21
unnamed: J9.19, U24.6
unnamed: JP2.1, R45.2, R46.1
unnamed: JP2.2, U27.3
unnamed: Q1.1, R9.1, R10.2
unnamed: Q2.1, R50.2
unnamed: Q2.2, R48.2
unnamed: R1.1, U5.24
unnamed: R2.1, U5.25
unnamed: R3.1, U3.14
unnamed: R6.1, U8.27
unnamed: R11.1, U11.27
unnamed: R11.2, U13.8
unnamed: R12.1, U11.28
unnamed: R12.2, U13.7
unnamed: R13.1, U11.29
unnamed: R13.2, U13.6
unnamed: R14.1, U11.30
unnamed: R14.2, U13.5
unnamed: R15.1, U11.31
unnamed: R15.2, U13.4
unnamed: R16.1, U11.32
unnamed: R16.2, U13.3
unnamed: R17.1, U11.33
unnamed: R17.2, U13.2
unnamed: R18.1, U11.34
unnamed: R18.2, U13.1
unnamed: R19.2, U17.6
unnamed: R20.2, U13.18
unnamed: R21.2, U13.17
unnamed: R22.2, U13.16
unnamed: R23.2, U13.15
unnamed: R24.2, U13.14
unnamed: R25.2, U13.13
unnamed: R26.2, U13.12
unnamed: R27.2, U13.11
unnamed: R28.2, U17.11
unnamed: R29.2, U17.12
unnamed: R30.2, U17.17
unnamed: R31.2, U17.15
unnamed: R33.1, R34.2, U22.1
unnamed: R37.1, U24.3
unnamed: R38.1, R39.1, U24.38
unnamed: R40.1, U24.4
unnamed: R41.2, U23.10, U23.13
unnamed: R51.2, U17.29
unnamed: U9.3, U11.37
unnamed: U19.2, U19.3
unnamed: U19.4, U19.5
unnamed: U20.3, U20.4, U20.9
unnamed: U21.10, U24.29
unnamed: U21.13, U24.27
unnamed: U23.1, U25.3
unnamed: U23.12, U26.3
unnamed: U26.2, U26.6
unnamed: U26.8, U26.12
PIO_IE: U10.11, U11.24
PIO_SEL: U2.15, U11.4
PSG_SEL: U2.11, U21.9, U21.11
RAM_SEL: U1.5, U6.20
RAS: U12.1, U19.9
RD: U5.21, U6.22, U8.22, U10.6, U11.35, U17.32, U20.5
RESET: R47.2, R48.1, U3.1, U5.26, U9.1, U10.17, U12.34, U17.21, U23.2, U24.23
ROM_SEL: U1.4, U8.20
ROW: U14.11, U19.8
RTSB: U3.5, U17.24
RXB: U3.3, U17.28
SCK: U3.19, U4.2
SD_DET: J1.1, R5.2, U3.13
SD_OE: U3.12, U4.1, U4.4, U4.10
SD_SS: U3.16, U4.5
SIO_SEL: U2.13, U17.35
SRL_CLK: U3.6, U10.7, U17.13, U17.14, U17.27
TXB: U3.2, U17.26
VDP_INT: R8.2, U5.17, U12.16
VDP_SEL: U2.12, U20.1
VRW: U12.11, U16.1, U18.27, U19.11
VWR: U16.11, U18.22, U19.10
WR: U5.22, U6.27, U20.10, U21.12

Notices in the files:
readme.md:
The LM80C/LM80C 64K schematics and source codes are released under the GNU GPL License 3.0 and in the form of "as is", without any kind of warranty: you can use them at your own risk.
